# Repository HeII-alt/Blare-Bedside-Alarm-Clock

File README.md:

# Blare Bedside Alarm Clock

A custom-designed, compact desktop alarm clock powered by the Seeed Studio XIAO ESP32C3 microcontroller.

---

## Screenshots and Renders

### 1. Exploded View

### 2. Schematic

### 3. PCB Layout

### 4. Case Top and Bottom

### 5. Assembled View

---

## Bill of Materials (BOM)

| Item | Qty | Description |
| :--- | :---: | :--- |
| **Microcontroller** | 1 | Seeed Studio XIAO ESP32C3 |
| **Switches** | 4 | MX-Style Keyboard Switches |
| **Keycaps** | 4 | White Blank DSA Keycaps |
| **Diodes** | 4 | Through-Hole 1N4148 Diodes |
| **Display** | 1 | 2.25in TFT Screen |
| **Buzzer** | 1 | 3.3V Piezo Buzzer |
| **Heatset Inserts** | 4 | M3x5x4 Heatset Inserts |
| **Screws** | 4 | M3x8mm Screws |

---

## License

Distributed under the MIT License.

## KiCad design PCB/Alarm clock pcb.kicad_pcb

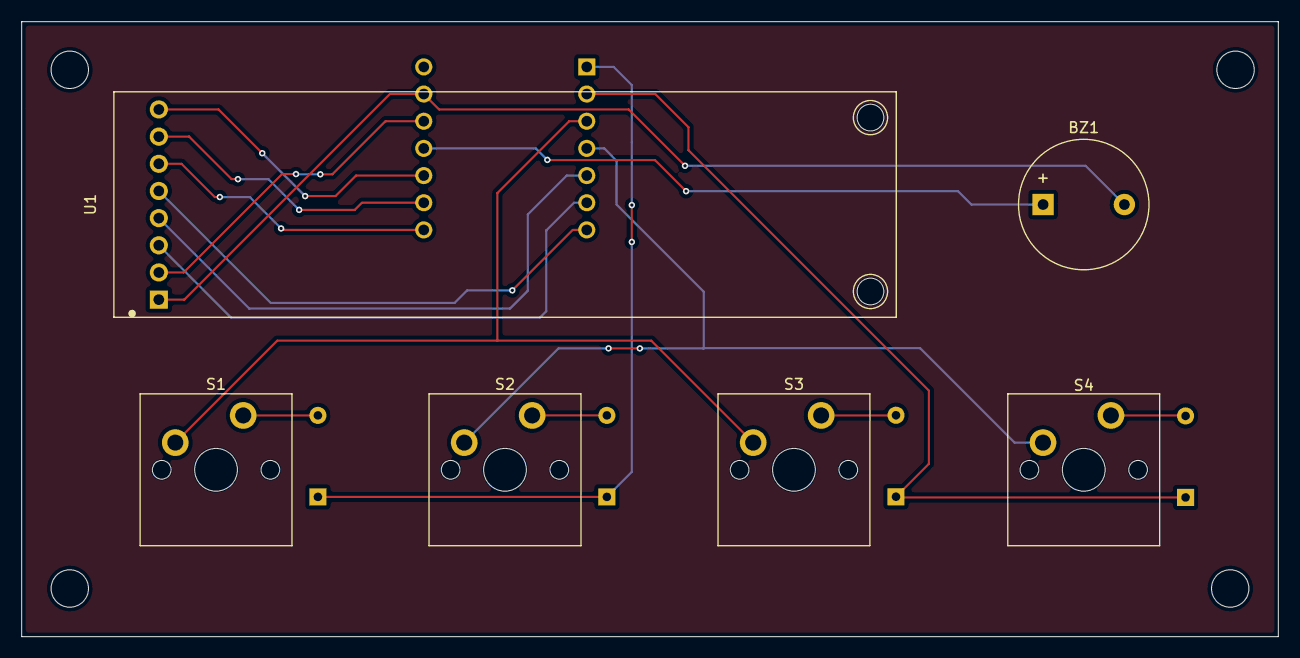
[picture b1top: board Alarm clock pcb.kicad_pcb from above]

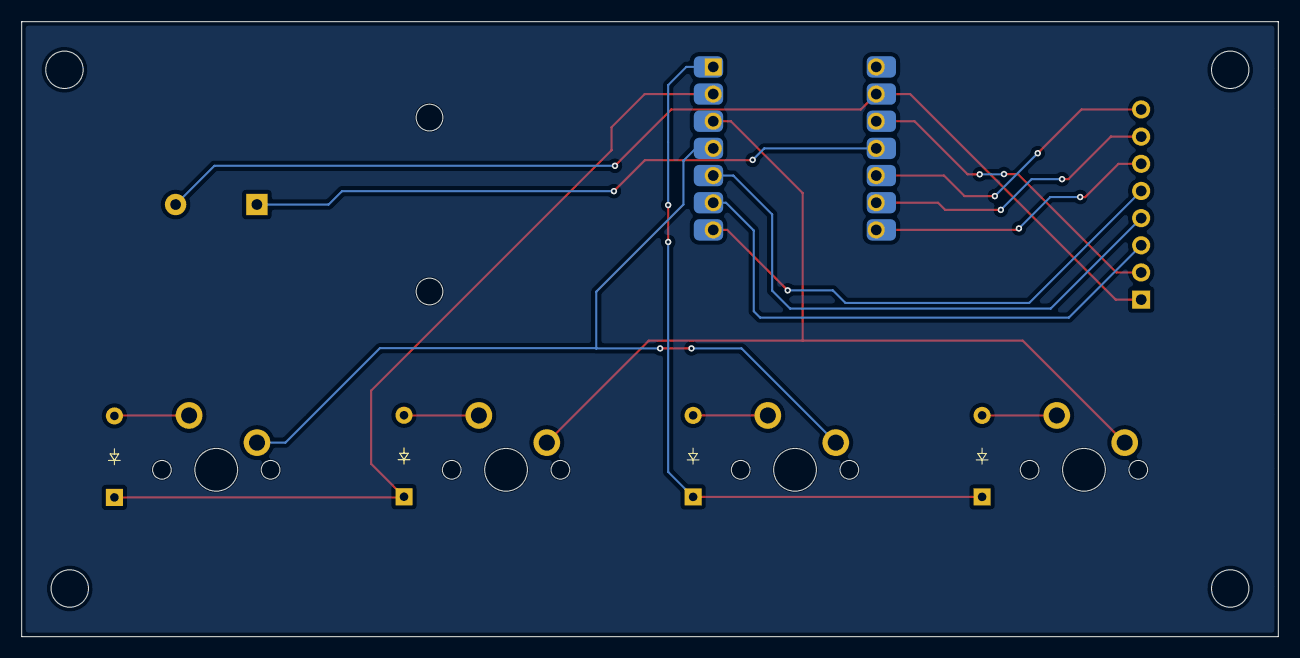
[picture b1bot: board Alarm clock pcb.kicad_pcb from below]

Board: 2 copper layers, 117.5 x 57.5 mm, 11 parts (5 on the bottom side), 17 nets.

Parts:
BZ1: Buzzer; Buzzer_12x9.5RM7.6
D1, D2, D3, D4: Diode_DO-35
S1, S2, S3, S4: MX_PCB_1.00u
U1: Display_ST7789_2.25in_76x284_8P
U2: MCU_Seeed_XIAO_RP2040; Seeed_XIAO_RP2040

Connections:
3.3 V: U1.2 (VCC), U2.12 (3V3)
BLK: U1.8 (BLK), U2.10 (PA5_A9_D9_MISO)
BUZZER: BZ1.1 (+), U2.11 (PA6_A10_D10_MOSI)
COLLUM 1: S1.1, S3.1, U2.3 (PA10_A2_D2)
COLLUM 2: S2.1, S4.1, U2.4 (PA11_A3_D3)
CS: U1.7 (CS), U2.9 (PA7_A8_D8_SCK)
DC: U1.6 (DC), U2.8 (PB09_A7_D7_RX)
GND: BZ1.2 (-), U1.1 (GND), U2.13 (GND)
unnamed: D1.2 (A), S1.2
unnamed: D2.2 (A), S2.2
unnamed: D3.2 (A), S3.2
unnamed: D4.2 (A), S4.2
RES: U1.5 (RES), U2.7 (PB08_A6_D6_TX)
Row 1: D1.1 (K), D2.1 (K), U2.1 (PA02_A0_D0)
Row 2: D3.1 (K), D4.1 (K), U2.2 (PA4_A1_D1)
SCL: U1.3 (SCL), U2.6 (PA9_A5_D5_SCL)
SDA: U1.4 (SDA), U2.5 (PA8_A4_D4_SDA)

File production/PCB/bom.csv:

Designator,Footprint,Quantity,Value,LCSC Part #
BZ1,Buzzer_12x9.5RM7.6,1,Buzzer,
"D1, D2, D3, D4",Diode_DO-35,4,~,
"S1, S2, S3, S4",MX_PCB_1.00u,4,~,
U1,Display_ST7789_2.25in_76x284_8P,1,~,
U2,Seeed_XIAO_RP2040,1,MCU_Seeed_XIAO_RP2040,
